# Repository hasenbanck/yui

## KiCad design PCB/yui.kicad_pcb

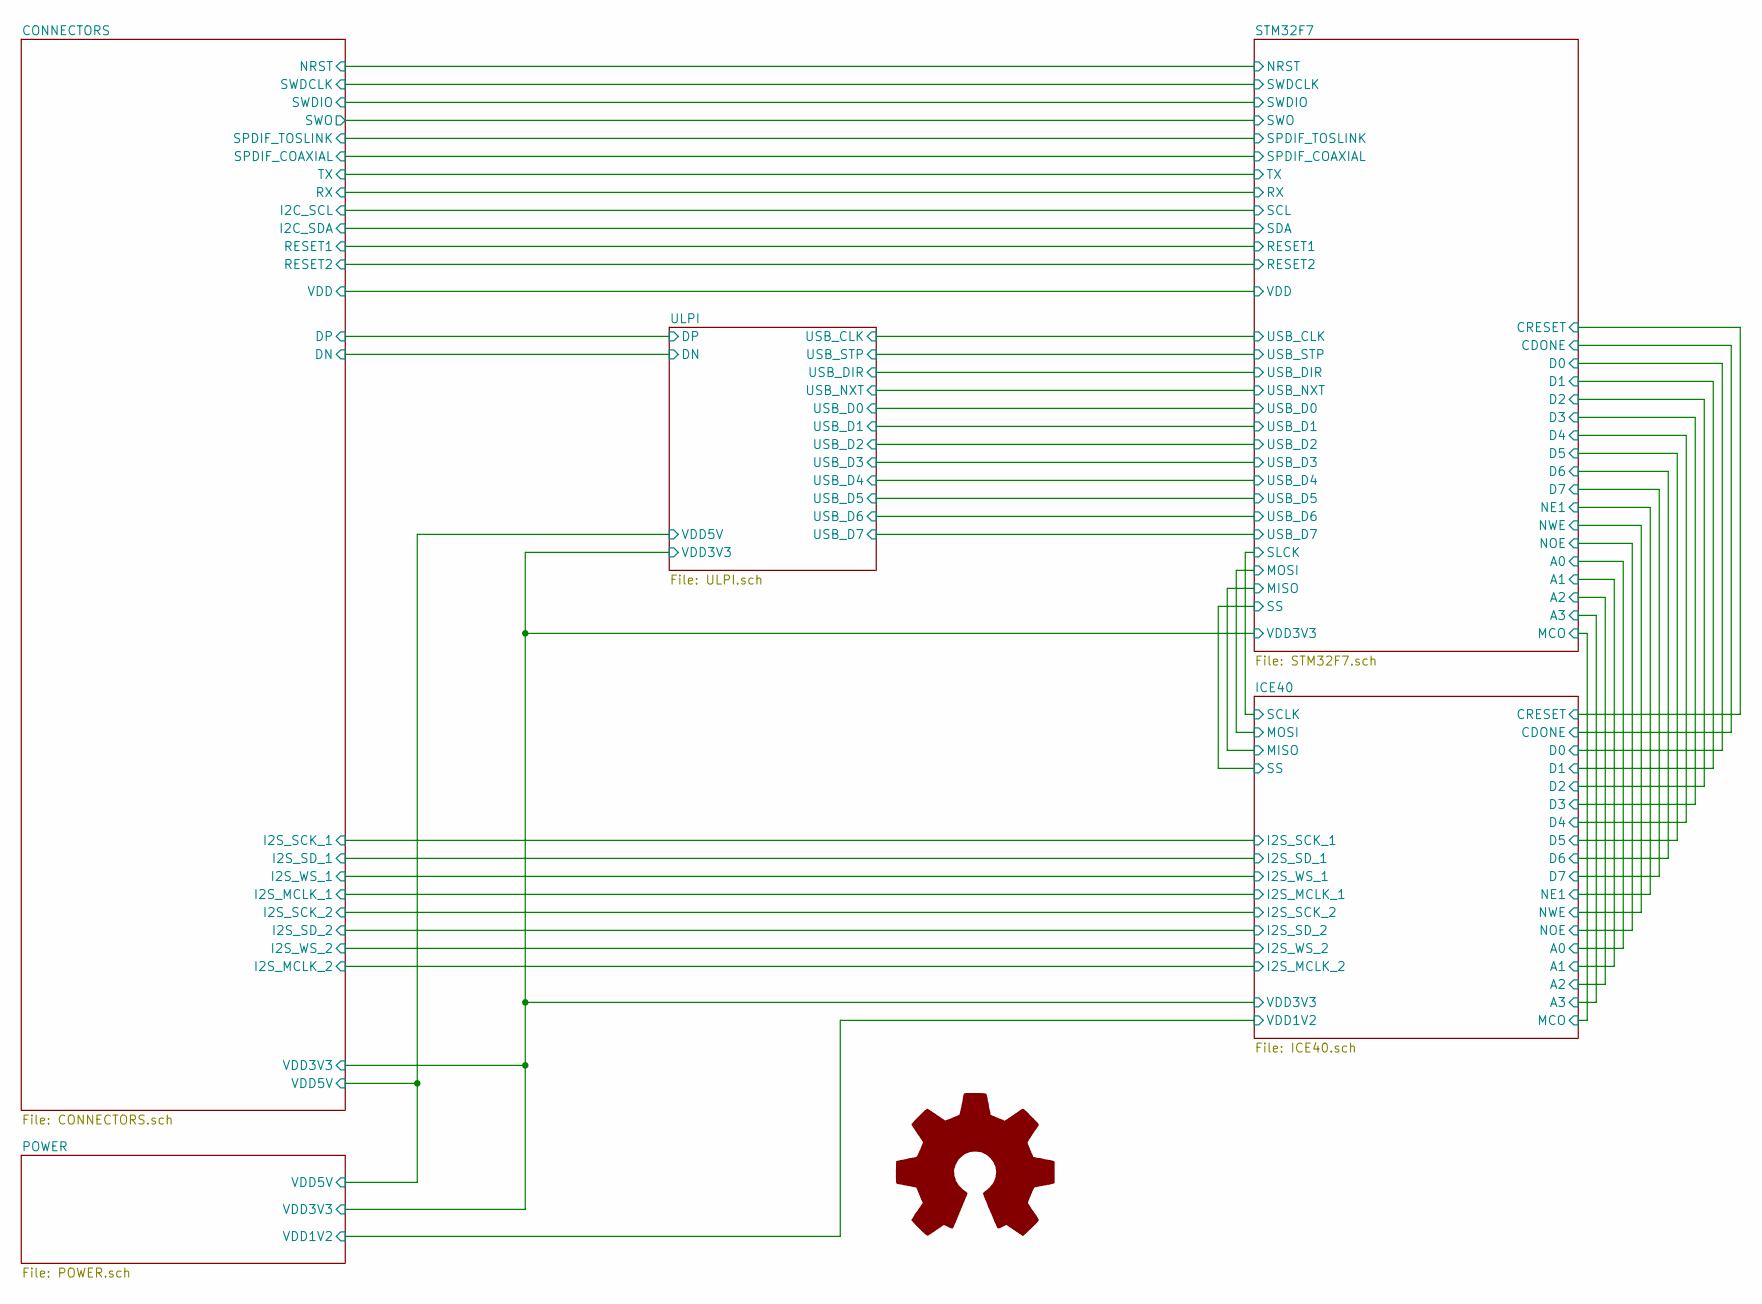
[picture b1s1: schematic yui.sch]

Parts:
LOGO1: Logo_Open_Hardware_Large; OSHW-Logo2_9.8x8mm_SilkScreen

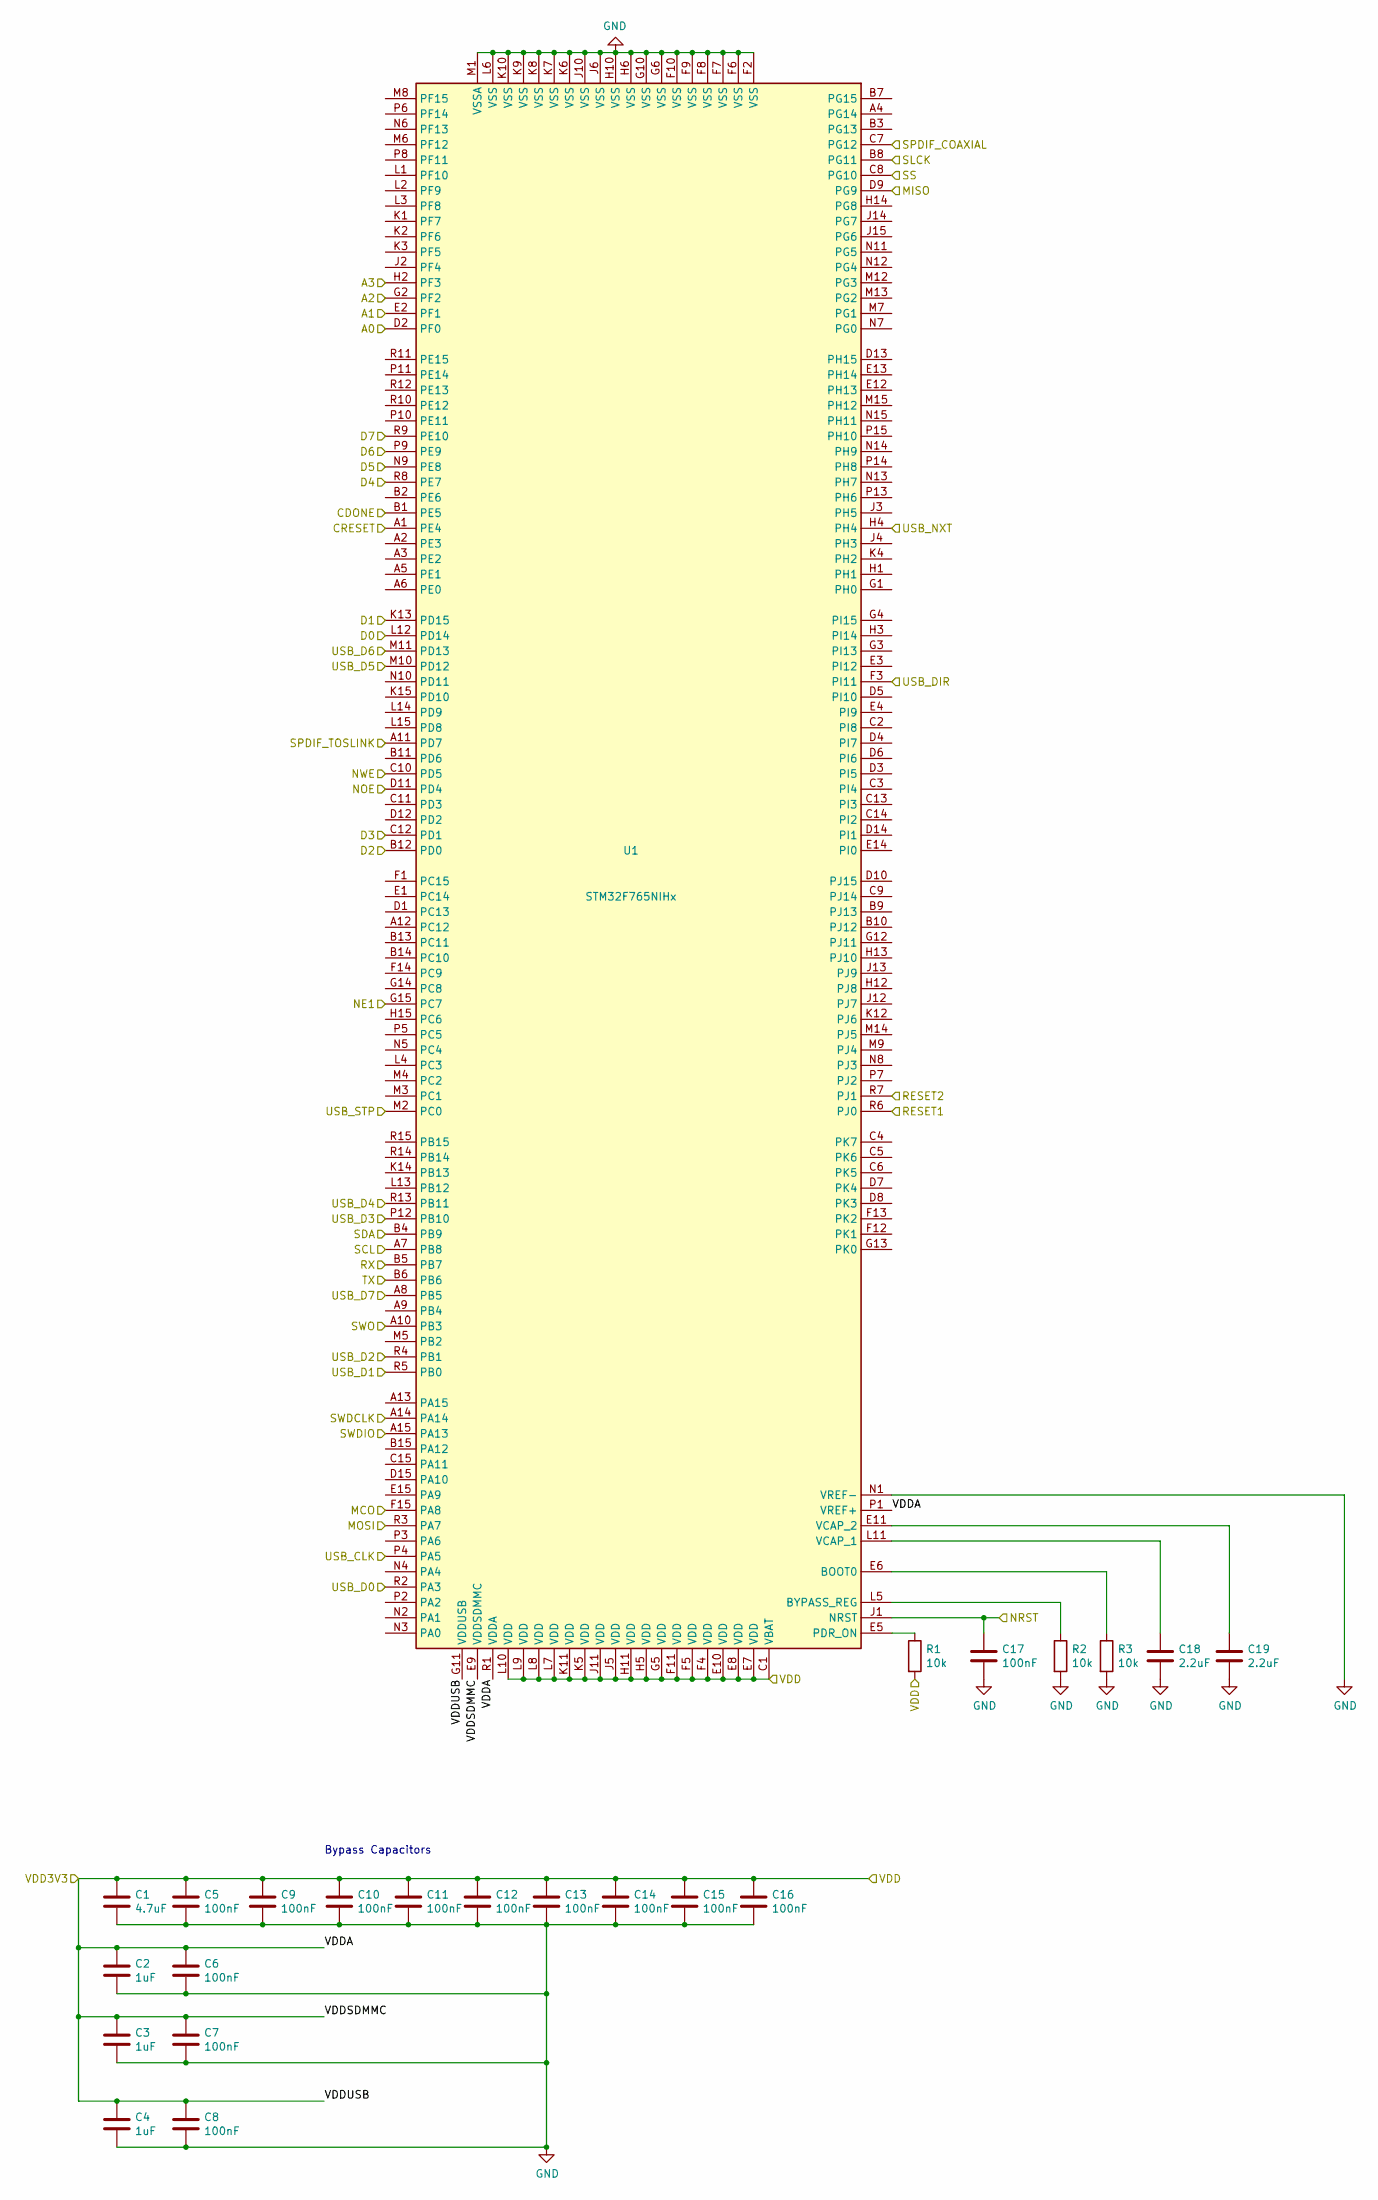
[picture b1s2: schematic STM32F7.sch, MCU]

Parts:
C1: 4.7uF; C_0603_1608Metric
C2, C3, C4: 1uF; C_0603_1608Metric
C5, C6, C7, C8, C9, C10, C11, C12, C13, C14, C15, C16, C17: 100nF; C_0603_1608Metric
C18, C19: 2.2uF; C_0603_1608Metric
R1, R2, R3: 10k; R_0603_1608Metric
U1: STM32F765NIHx; TFBGA-216_13x13mm_Layout15x15_P0.8mm

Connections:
/CONNECTORS/I2C_SCL: U1.A7 (PB8); also elsewhere on the board
/CONNECTORS/I2C_SDA: U1.B4 (PB9); also elsewhere on the board
/CONNECTORS/NRST: C17.2, U1.J1 (NRST); also elsewhere on the board
/CONNECTORS/RESET1: U1.R6 (PJ0); also elsewhere on the board
/CONNECTORS/RESET2: U1.R7 (PJ1); also elsewhere on the board
/CONNECTORS/RX: U1.B5 (PB7); also elsewhere on the board
/CONNECTORS/SPDIF_COAXIAL: U1.C7 (PG12); also elsewhere on the board
/CONNECTORS/SPDIF_TOSLINK: U1.A11 (PD7); also elsewhere on the board
/CONNECTORS/SWDCLK: U1.A14; also elsewhere on the board
/CONNECTORS/SWDIO: U1.A15 (PA13); also elsewhere on the board
/CONNECTORS/SWO: U1.A10 (PB3); also elsewhere on the board
/CONNECTORS/TX: U1.B6; also elsewhere on the board
/CONNECTORS/VDD: C1.1, C2.1, C3.1, C4.1, C5.1, C6.1, C7.1, C8.1, C9.1, C10.1, C11.1, C12.1, C13.1, C14.1, C15.1, C16.1, R1.2, U1.C1 (VBAT), U1.E7 (VDD), U1.E8 (VDD), U1.E9 (VDDSDMMC), U1.E10 (VDD), U1.F4 (VDD), U1.F5 (VDD), U1.F11 (VDD), U1.G5 (VDD), U1.G11 (VDDUSB), U1.H5 (VDD), U1.H11 (VDD), U1.J5 (VDD), U1.J11 (VDD), U1.K5 (VDD), U1.K11 (VDD), U1.L7 (VDD), U1.L8 (VDD), U1.L9 (VDD), U1.L10 (VDD), U1.P1 (VREF+), U1.R1 (VDDA); also elsewhere on the board
/ICE40/A0: U1.D2 (PF0); also elsewhere on the board
/ICE40/A1: U1.E2 (PF1); also elsewhere on the board
/ICE40/A2: U1.G2 (PF2); also elsewhere on the board
/ICE40/A3: U1.H2 (PF3); also elsewhere on the board
/ICE40/CDONE: U1.B1 (PE5); also elsewhere on the board
/ICE40/CRESET: U1.A1 (PE4); also elsewhere on the board
/ICE40/D0: U1.L12 (PD14); also elsewhere on the board
/ICE40/D1: U1.K13 (PD15); also elsewhere on the board
/ICE40/D2: U1.B12 (PD0); also elsewhere on the board
/ICE40/D3: U1.C12 (PD1); also elsewhere on the board
/ICE40/D4: U1.R8 (PE7); also elsewhere on the board
/ICE40/D5: U1.N9 (PE8); also elsewhere on the board
/ICE40/D6: U1.P9 (PE9); also elsewhere on the board
/ICE40/D7: U1.R9 (PE10); also elsewhere on the board
/ICE40/MCO: U1.F15 (PA8); also elsewhere on the board
/ICE40/MISO: U1.D9 (PG9); also elsewhere on the board
/ICE40/MOSI: U1.R3 (PA7); also elsewhere on the board
/ICE40/NE1: U1.G15 (PC7); also elsewhere on the board
/ICE40/NOE: U1.D11 (PD4); also elsewhere on the board
/ICE40/NWE: U1.C10 (PD5); also elsewhere on the board
/ICE40/SCLK: U1.B8 (PG11); also elsewhere on the board
/ICE40/SS: U1.C8 (PG10); also elsewhere on the board
/STM32F7/USB_CLK: U1.P4 (PA5); also elsewhere on the board
/STM32F7/USB_D0: U1.R2 (PA3); also elsewhere on the board
/STM32F7/USB_D1: U1.R5 (PB0); also elsewhere on the board
/STM32F7/USB_D2: U1.R4 (PB1); also elsewhere on the board
/STM32F7/USB_D3: U1.P12 (PB10); also elsewhere on the board
/STM32F7/USB_D4: U1.R13 (PB11); also elsewhere on the board
/STM32F7/USB_D5: U1.M10 (PD12); also elsewhere on the board
/STM32F7/USB_D6: U1.M11 (PD13); also elsewhere on the board
/STM32F7/USB_D7: U1.A8 (PB5); also elsewhere on the board
/STM32F7/USB_DIR: U1.F3 (PI11); also elsewhere on the board
/STM32F7/USB_NXT: U1.H4; also elsewhere on the board
/STM32F7/USB_STP: U1.M2 (PC0); also elsewhere on the board
GND: C1.2, C2.2, C3.2, C4.2, C5.2, C6.2, C7.2, C8.2, C9.2, C10.2, C11.2, C12.2, C13.2, C14.2, C15.2, C16.2, C17.1, C18.1, C19.1, R2.2, R3.2, U1.F2 (VSS), U1.F6 (VSS), U1.F7 (VSS), U1.F8 (VSS), U1.F9 (VSS), U1.F10 (VSS), U1.G6 (VSS), U1.G10 (VSS), U1.H6 (VSS), U1.H10 (VSS), U1.J6 (VSS), U1.J10 (VSS), U1.K6 (VSS), U1.K7 (VSS), U1.K8 (VSS), U1.K9 (VSS), U1.K10 (VSS), U1.L6 (VSS), U1.M1 (VSSA), U1.N1 (VREF-); also elsewhere on the board
unnamed: C18.2, U1.L11 (VCAP_1)
unnamed: C19.2, U1.E11 (VCAP_2)
unnamed: R1.1, U1.E5 (PDR_ON)
unnamed: R2.1, U1.L5 (BYPASS_REG)
unnamed: R3.1, U1.E6 (BOOT0)

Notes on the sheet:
Bypass Capacitors

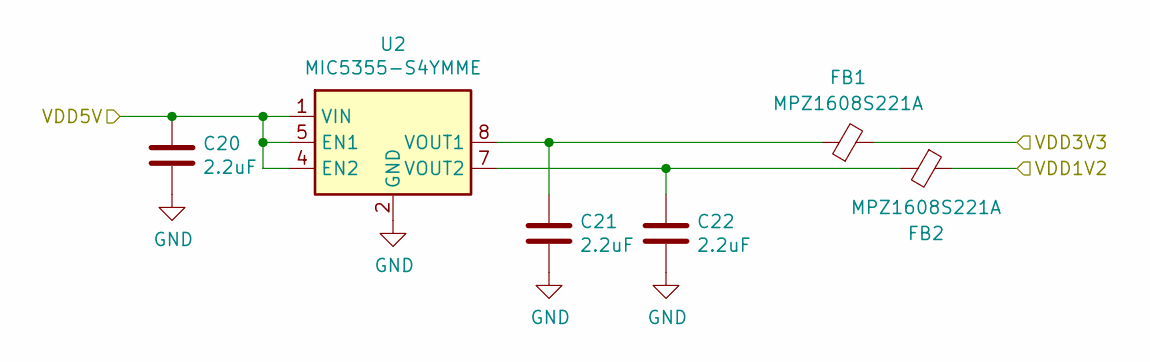
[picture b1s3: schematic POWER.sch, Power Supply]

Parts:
C20, C21, C22: 2.2uF; C_0603_1608Metric
FB1, FB2: MPZ1608S221A; L_0603_1608Metric
U2: MIC5355-S4YMME; MSOP-8-1EP_3x3mm_P0.65mm_EP2.54x2.8mm_ThermalVias

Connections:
/CONNECTORS/VDD: FB1.2; also elsewhere on the board
/CONNECTORS/VDD5V: C20.1, U2.1 (VIN), U2.4 (EN2), U2.5 (EN1); also elsewhere on the board
/ICE40/VDD1V2: FB2.1; also elsewhere on the board
GND: C20.2, C21.2, C22.2, U2.2 (GND), U2.9 (GND); also elsewhere on the board
unnamed: C21.1, FB1.1, U2.8 (VOUT1)
unnamed: C22.1, FB2.2, U2.7 (VOUT2)

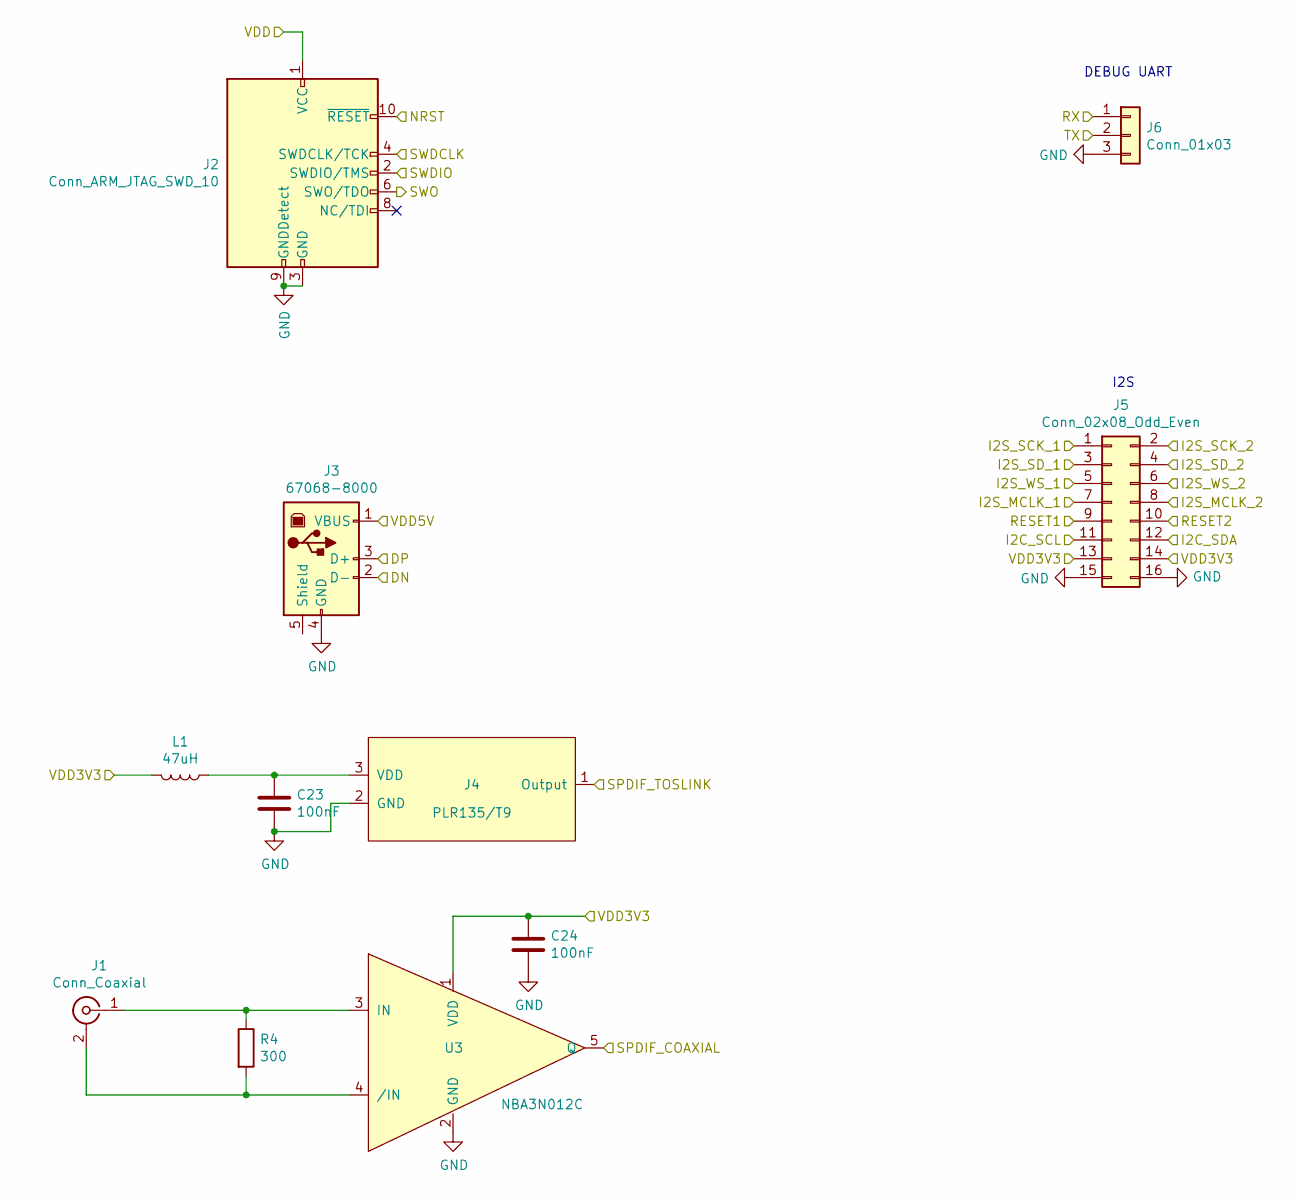
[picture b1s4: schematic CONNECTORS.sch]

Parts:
C23, C24: 100nF; C_0603_1608Metric
J1: Conn_Coaxial; CUI_RCJ-017
J2: Conn_ARM_JTAG_SWD_10; PinHeader_2x05_P1.27mm_Vertical_SMD
J3: 67068-8000
J4: PLR135/T9; PLR135-T9
J5: Conn_02x08_Odd_Even; PinHeader_2x08_P2.54mm_Vertical
J6: Conn_01x03; PinHeader_1x03_P2.54mm_Vertical
L1: 47uH; L_0805_2012Metric
R4: 300; R_0603_1608Metric
U3: NBA3N012C; TSOT-23-5

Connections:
/CONNECTORS/DN: J3.2 (D-); also elsewhere on the board
/CONNECTORS/DP: J3.3 (D+); also elsewhere on the board
/CONNECTORS/I2C_SCL: J5.11; also elsewhere on the board
/CONNECTORS/I2C_SDA: J5.12; also elsewhere on the board
/CONNECTORS/I2S_MCLK_1: J5.7; also elsewhere on the board
/CONNECTORS/I2S_MCLK_2: J5.8; also elsewhere on the board
/CONNECTORS/I2S_SCK_1: J5.1; also elsewhere on the board
/CONNECTORS/I2S_SCK_2: J5.2; also elsewhere on the board
/CONNECTORS/I2S_SD_1: J5.3; also elsewhere on the board
/CONNECTORS/I2S_SD_2: J5.4; also elsewhere on the board
/CONNECTORS/I2S_WS_1: J5.5; also elsewhere on the board
/CONNECTORS/I2S_WS_2: J5.6; also elsewhere on the board
/CONNECTORS/NRST: J2.10 (~RESET~); also elsewhere on the board
/CONNECTORS/RESET1: J5.9; also elsewhere on the board
/CONNECTORS/RESET2: J5.10; also elsewhere on the board
/CONNECTORS/RX: J6.1; also elsewhere on the board
/CONNECTORS/SPDIF_COAXIAL: U3.5 (Q); also elsewhere on the board
/CONNECTORS/SPDIF_TOSLINK: J4.1 (Output); also elsewhere on the board
/CONNECTORS/SWDCLK: J2.4 (SWDCLK/TCK); also elsewhere on the board
/CONNECTORS/SWDIO: J2.2 (SWDIO/TMS); also elsewhere on the board
/CONNECTORS/SWO: J2.6 (SWO/TDO); also elsewhere on the board
/CONNECTORS/TX: J6.2; also elsewhere on the board
/CONNECTORS/VDD: C24.1, J2.1 (VCC), J5.13, J5.14, L1.2, U3.1 (VDD); also elsewhere on the board
/CONNECTORS/VDD5V: J3.1 (VBUS); also elsewhere on the board
GND: C23.2, C24.2, J2.3 (GND), J2.5 (GND), J2.9 (GNDDetect), J3.4 (GND), J4.2 (GND), J5.15, J5.16, J6.3, U3.2 (GND); also elsewhere on the board
unnamed: C23.1, J4.3 (VDD), L1.1
unnamed: J1.1 (In), R4.1, U3.3 (IN)
unnamed: J1.2 (Ext), R4.2, U3.4 (/IN)

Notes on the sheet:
DEBUG UART
I2S

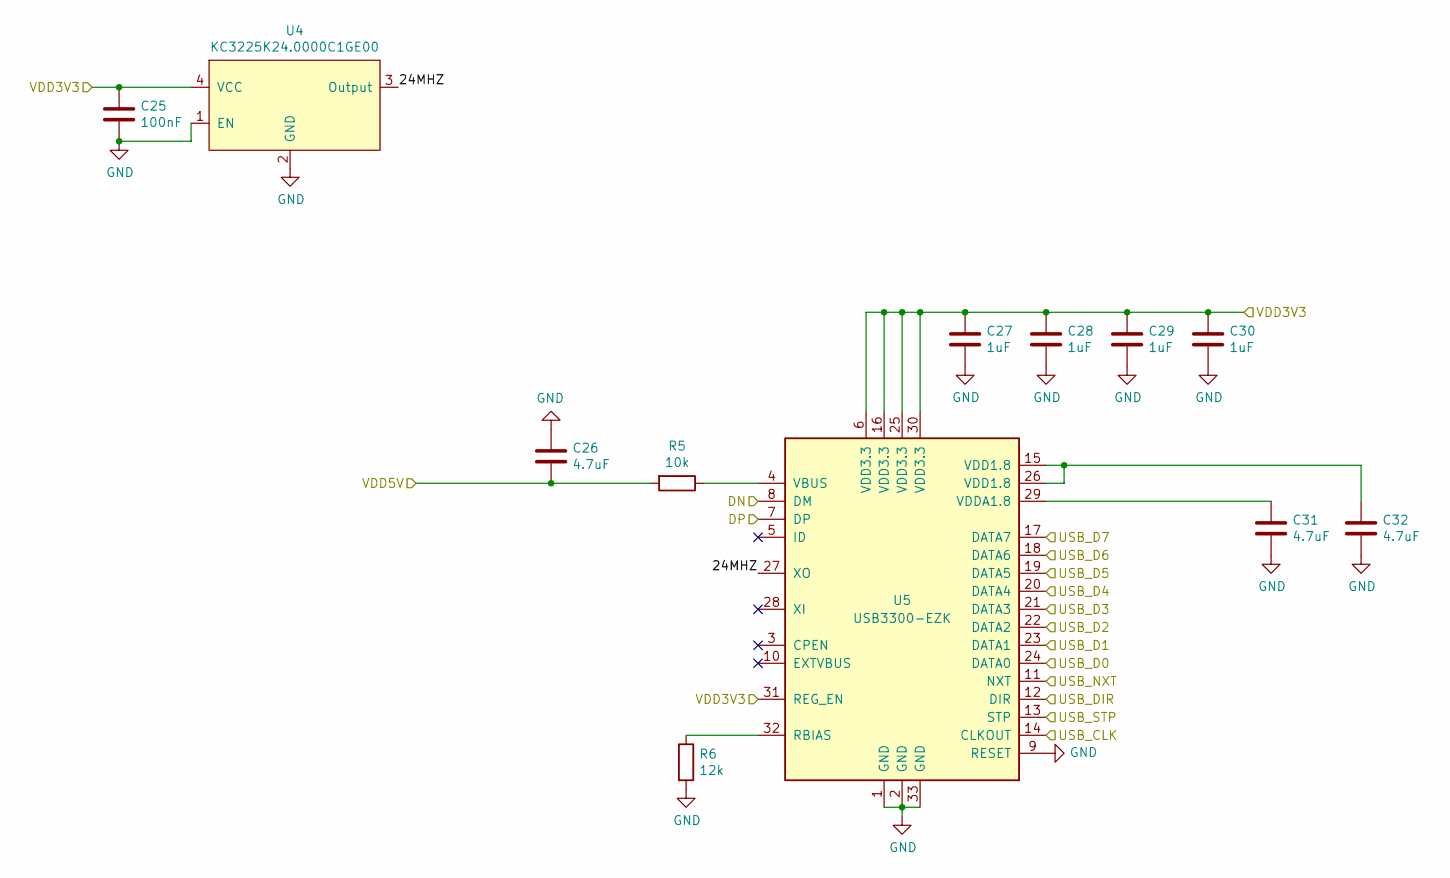
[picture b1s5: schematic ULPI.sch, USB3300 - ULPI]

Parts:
C25: 100nF; C_0603_1608Metric
C26, C31, C32: 4.7uF; C_0603_1608Metric
C27, C28, C29, C30: 1uF; C_0603_1608Metric
R5: 10k; R_0603_1608Metric
R6: 12k; R_0603_1608Metric
U4: KC3225K24.0000C1GE00; KC3225K
U5: USB3300-EZK; QFN-32-1EP_5x5mm_P0.5mm_EP3.45x3.45mm

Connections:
/CONNECTORS/DN: U5.8 (DM); also elsewhere on the board
/CONNECTORS/DP: U5.7 (DP); also elsewhere on the board
/CONNECTORS/VDD: C25.1, C27.1, C28.1, C29.1, C30.1, U4.4 (VCC), U5.6 (VDD3.3), U5.16 (VDD3.3), U5.25 (VDD3.3), U5.30 (VDD3.3), U5.31 (REG_EN); also elsewhere on the board
/CONNECTORS/VDD5V: C26.2, R5.2; also elsewhere on the board
/STM32F7/USB_CLK: U5.14 (CLKOUT); also elsewhere on the board
/STM32F7/USB_D0: U5.24 (DATA0); also elsewhere on the board
/STM32F7/USB_D1: U5.23 (DATA1); also elsewhere on the board
/STM32F7/USB_D2: U5.22 (DATA2); also elsewhere on the board
/STM32F7/USB_D3: U5.21 (DATA3); also elsewhere on the board
/STM32F7/USB_D4: U5.20 (DATA4); also elsewhere on the board
/STM32F7/USB_D5: U5.19 (DATA5); also elsewhere on the board
/STM32F7/USB_D6: U5.18 (DATA6); also elsewhere on the board
/STM32F7/USB_D7: U5.17 (DATA7); also elsewhere on the board
/STM32F7/USB_DIR: U5.12 (DIR); also elsewhere on the board
/STM32F7/USB_NXT: U5.11 (NXT); also elsewhere on the board
/STM32F7/USB_STP: U5.13 (STP); also elsewhere on the board
/ULPI/24MHZ: U4.3 (Output), U5.27 (XO)
GND: C25.2, C26.1, C27.2, C28.2, C29.2, C30.2, C31.2, C32.2, R6.2, U4.1 (EN), U4.2 (GND), U5.1 (GND), U5.2 (GND), U5.9 (RESET), U5.33 (GND); also elsewhere on the board
unnamed: C31.1, U5.29 (VDDA1.8)
unnamed: C32.1, U5.15 (VDD1.8), U5.26 (VDD1.8)
unnamed: R5.1, U5.4 (VBUS)
unnamed: R6.1, U5.32 (RBIAS)

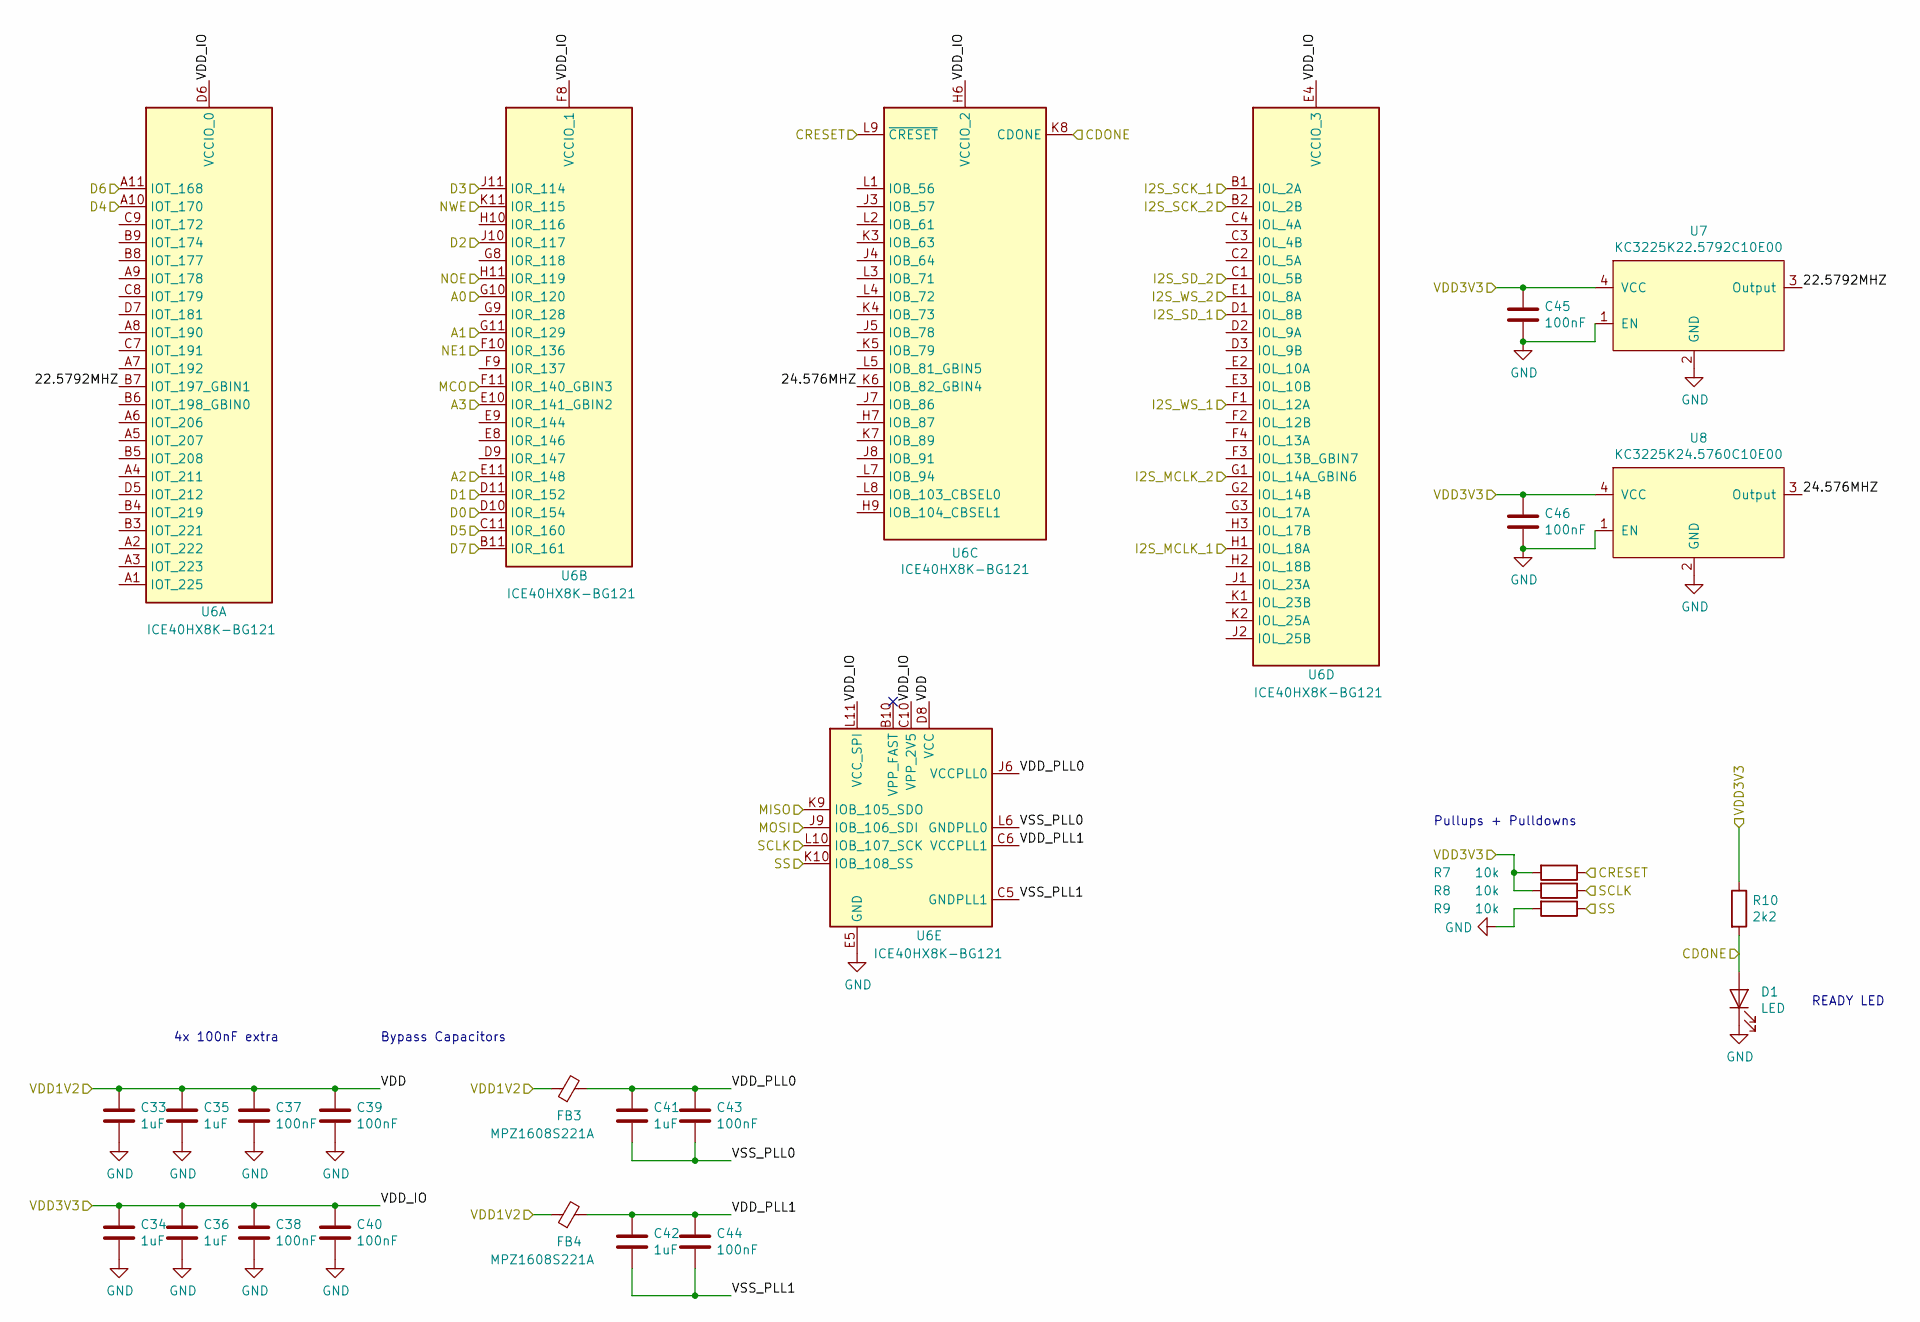
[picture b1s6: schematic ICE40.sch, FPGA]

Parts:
C33, C34, C35, C36, C41, C42: 1uF; C_0603_1608Metric
C37, C38, C39, C40, C43, C44, C45, C46: 100nF; C_0603_1608Metric
D1: LED; LED_0603_1608Metric
FB3, FB4: MPZ1608S221A; L_0603_1608Metric
R7, R8, R9: 10k; R_0603_1608Metric
R10: 2k2; R_0603_1608Metric
U6: ICE40HX8K-BG121; BGA-121_9.0x9.0mm_Layout11x11_P0.8mm_Ball0.4mm_Pad0.35mm_NS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
U7: KC3225K22.5792C10E00; KC3225K
U8: KC3225K24.5760C10E00; KC3225K

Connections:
/CONNECTORS/I2S_MCLK_1: U6.H1 (IOL_18A); also elsewhere on the board
/CONNECTORS/I2S_MCLK_2: U6.G1 (IOL_14A_GBIN6); also elsewhere on the board
/CONNECTORS/I2S_SCK_1: U6.B1 (IOL_2A); also elsewhere on the board
/CONNECTORS/I2S_SCK_2: U6.B2 (IOL_2B); also elsewhere on the board
/CONNECTORS/I2S_SD_1: U6.D1 (IOL_8B); also elsewhere on the board
/CONNECTORS/I2S_SD_2: U6.C1 (IOL_5B); also elsewhere on the board
/CONNECTORS/I2S_WS_1: U6.F1 (IOL_12A); also elsewhere on the board
/CONNECTORS/I2S_WS_2: U6.E1 (IOL_8A); also elsewhere on the board
/CONNECTORS/VDD: C34.1, C36.1, C38.1, C40.1, C45.1, C46.1, R7.2, R8.2, R10.1, U6.C10 (VPP_2V5), U6.D6 (VCCIO_0), U6.E4 (VCCIO_3), U6.F8 (VCCIO_1), U6.G4 (VCCIO_3), U6.H6 (VCCIO_2), U6.L11 (VCC_SPI), U7.4 (VCC), U8.4 (VCC); also elsewhere on the board
/ICE40/22.5792MHZ: U6.B7 (IOT_197_GBIN1), U7.3 (Output)
/ICE40/24.576MHZ: U6.K6 (IOB_82_GBIN4), U8.3 (Output)
/ICE40/A0: U6.G10 (IOR_120); also elsewhere on the board
/ICE40/A1: U6.G11 (IOR_129); also elsewhere on the board
/ICE40/A2: U6.E11 (IOR_148); also elsewhere on the board
/ICE40/A3: U6.E10 (IOR_141_GBIN2); also elsewhere on the board
/ICE40/CDONE: D1.2 (A), R10.2, U6.K8 (CDONE); also elsewhere on the board
/ICE40/CRESET: R7.1, U6.L9 (~CRESET); also elsewhere on the board
/ICE40/D0: U6.D10 (IOR_154); also elsewhere on the board
/ICE40/D1: U6.D11 (IOR_152); also elsewhere on the board
/ICE40/D2: U6.J10 (IOR_117); also elsewhere on the board
/ICE40/D3: U6.J11 (IOR_114); also elsewhere on the board
/ICE40/D4: U6.A10 (IOT_170); also elsewhere on the board
/ICE40/D5: U6.C11 (IOR_160); also elsewhere on the board
/ICE40/D6: U6.A11 (IOT_168); also elsewhere on the board
/ICE40/D7: U6.B11 (IOR_161); also elsewhere on the board
/ICE40/MCO: U6.F11 (IOR_140_GBIN3); also elsewhere on the board
/ICE40/MISO: U6.K9 (IOB_105_SDO); also elsewhere on the board
/ICE40/MOSI: U6.J9 (IOB_106_SDI); also elsewhere on the board
/ICE40/NE1: U6.F10 (IOR_136); also elsewhere on the board
/ICE40/NOE: U6.H11 (IOR_119); also elsewhere on the board
/ICE40/NWE: U6.K11 (IOR_115); also elsewhere on the board
/ICE40/SCLK: R8.1, U6.L10 (IOB_107_SCK); also elsewhere on the board
/ICE40/SS: R9.1, U6.K10 (IOB_108_SS); also elsewhere on the board
/ICE40/VDD1V2: C33.1, C35.1, C37.1, C39.1, FB3.1, FB4.1, U6.D4 (VCC), U6.D8 (VCC), U6.H4 (VCC), U6.H8 (VCC); also elsewhere on the board
/ICE40/VDD_PLL0: C41.1, C43.1, FB3.2, U6.J6 (VCCPLL0)
/ICE40/VDD_PLL1: C42.1, C44.1, FB4.2, U6.C6 (VCCPLL1)
/ICE40/VSS_PLL0: C41.2, C43.2, U6.L6 (GNDPLL0)
/ICE40/VSS_PLL1: C42.2, C44.2, U6.C5 (GNDPLL1)
GND: C33.2, C34.2, C35.2, C36.2, C37.2, C38.2, C39.2, C40.2, C45.2, C46.2, D1.1 (K), R9.2, U6.E5 (GND), U6.E6 (GND), U6.E7 (GND), U6.F5 (GND), U6.F6 (GND), U6.F7 (GND), U6.G5 (GND), U6.G6 (GND), U6.G7 (GND), U6.H5 (GND), U7.1 (EN), U7.2 (GND), U8.1 (EN), U8.2 (GND); also elsewhere on the board

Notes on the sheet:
Bypass Capacitors
READY LED
Pullups + Pulldowns
4x 100nF extra

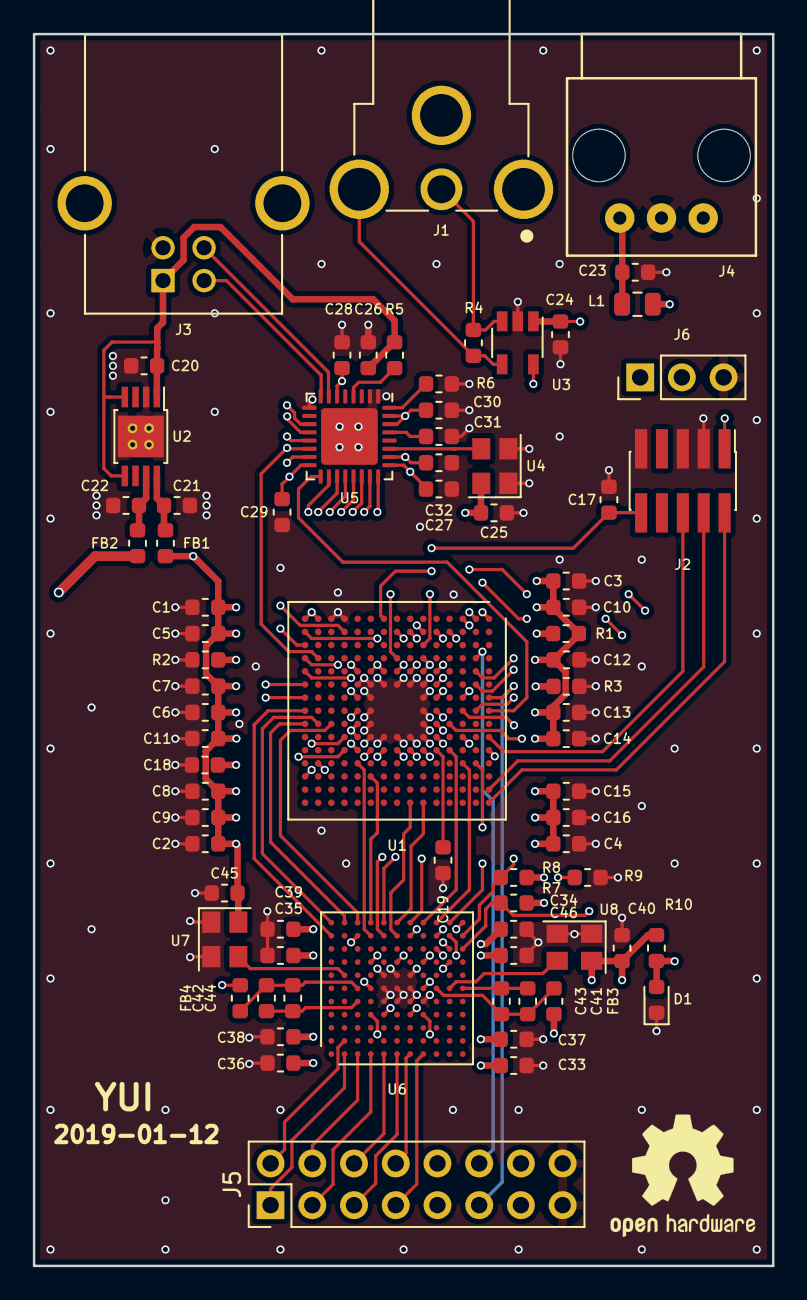
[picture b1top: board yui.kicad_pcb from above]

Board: 4 copper layers, 45.0 x 75.0 mm, 77 parts (0 on the bottom side), 81 nets.

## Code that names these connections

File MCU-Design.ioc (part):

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Mcu.Name=STM32F765N(G-I)Hx
Mcu.Package=TFBGA216
Mcu.UserName=STM32F765NIHx
PA13.Mode=Trace_Asynchronous_SW
PA13.Signal=SYS_JTMS-SWDIO
PA14.Mode=Trace_Asynchronous_SW
PA14.Signal=SYS_JTCK-SWCLK
PA3.Mode=Device_HS
PA3.Signal=USB_OTG_HS_ULPI_D0
PA5.Mode=Device_HS
PA5.Signal=USB_OTG_HS_ULPI_CK
PA7.Mode=Full_Duplex_Master
PA7.Signal=SPI1_MOSI
PA8.Mode=Clock-out-1
PA8.Signal=RCC_MCO_1
PB0.Mode=Device_HS
PB0.Signal=USB_OTG_HS_ULPI_D1
PB1.Mode=Device_HS
PB1.Signal=USB_OTG_HS_ULPI_D2
PB10.Mode=Device_HS
PB10.Signal=USB_OTG_HS_ULPI_D3
PB11.Mode=Device_HS
PB11.Signal=USB_OTG_HS_ULPI_D4
PB12.Mode=Device_HS
PB12.Signal=USB_OTG_HS_ULPI_D5
PB13.Mode=Device_HS
PB13.Signal=USB_OTG_HS_ULPI_D6
PB3.Mode=Trace_Asynchronous_SW
PB3.Signal=SYS_JTDO-SWO
PB5.Mode=Device_HS
PB5.Signal=USB_OTG_HS_ULPI_D7
PB6.Mode=Asynchronous
PB6.Signal=USART1_TX
PB7.Mode=Asynchronous
PB7.Signal=USART1_RX
PB8.Mode=I2C
PB8.Signal=I2C1_SCL
PB9.Mode=I2C
PB9.Signal=I2C1_SDA
PC0.Mode=Device_HS
PC0.Signal=USB_OTG_HS_ULPI_STP
PC7.Mode=NorPsramChipSelect1_1
PC7.Signal=FMC_NE1
PD0.Signal=FMC_D2_DA2
PD1.Signal=FMC_D3_DA3
PD14.Signal=FMC_D0_DA0
PD15.Signal=FMC_D1_DA1
PD4.Signal=FMC_NOE
PD5.Signal=FMC_NWE
PD7.Mode=IN0
PD7.Signal=SPDIFRX_IN0
PE10.Signal=FMC_D7_DA7
PE4.GPIOParameters=GPIO_Label
PE4.GPIO_Label=CDONE
PE4.Signal=GPIO_Input
PE5.GPIOParameters=GPIO_Label
PE5.GPIO_Label=CRESET
PE5.Signal=GPIO_Output
PE7.Signal=FMC_D4_DA4
PE8.Signal=FMC_D5_DA5
PE9.Signal=FMC_D6_DA6
PF0.Signal=FMC_A0
PF1.Signal=FMC_A1
PF2.Signal=FMC_A2
PF3.Signal=FMC_A3
PG10.Mode=NSS_Signal_Hard_Output
PG10.Signal=SPI1_NSS
PG11.Mode=Full_Duplex_Master
PG11.Signal=SPI1_SCK
PG12.Mode=IN1
PG12.Signal=SPDIFRX_IN1
PG9.Mode=Full_Duplex_Master
PG9.Signal=SPI1_MISO
PH4.Mode=Device_HS
PH4.Signal=USB_OTG_HS_ULPI_NXT
PI11.Mode=Device_HS
PI11.Signal=USB_OTG_HS_ULPI_DIR
PJ0.GPIOParameters=GPIO_Label
PJ0.GPIO_Label=RESET1
PJ0.Signal=GPIO_Output
PJ1.GPIOParameters=GPIO_Label
PJ1.GPIO_Label=RESET2
PJ1.Signal=GPIO_Output
RCC.HSE_VALUE=25000000
RCC.SYSCLKFreq_VALUE=216000000
RCC.SYSCLKSource=RCC_SYSCLKSOURCE_PLLCLK
board=custom

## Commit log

2019-01-10 Add gitignore for the PCB folder
2019-01-10 Add first design of the YUI I2S interface
2019-01-10 Attach LICENSE file for the design
2019-01-12 First fully routed version
